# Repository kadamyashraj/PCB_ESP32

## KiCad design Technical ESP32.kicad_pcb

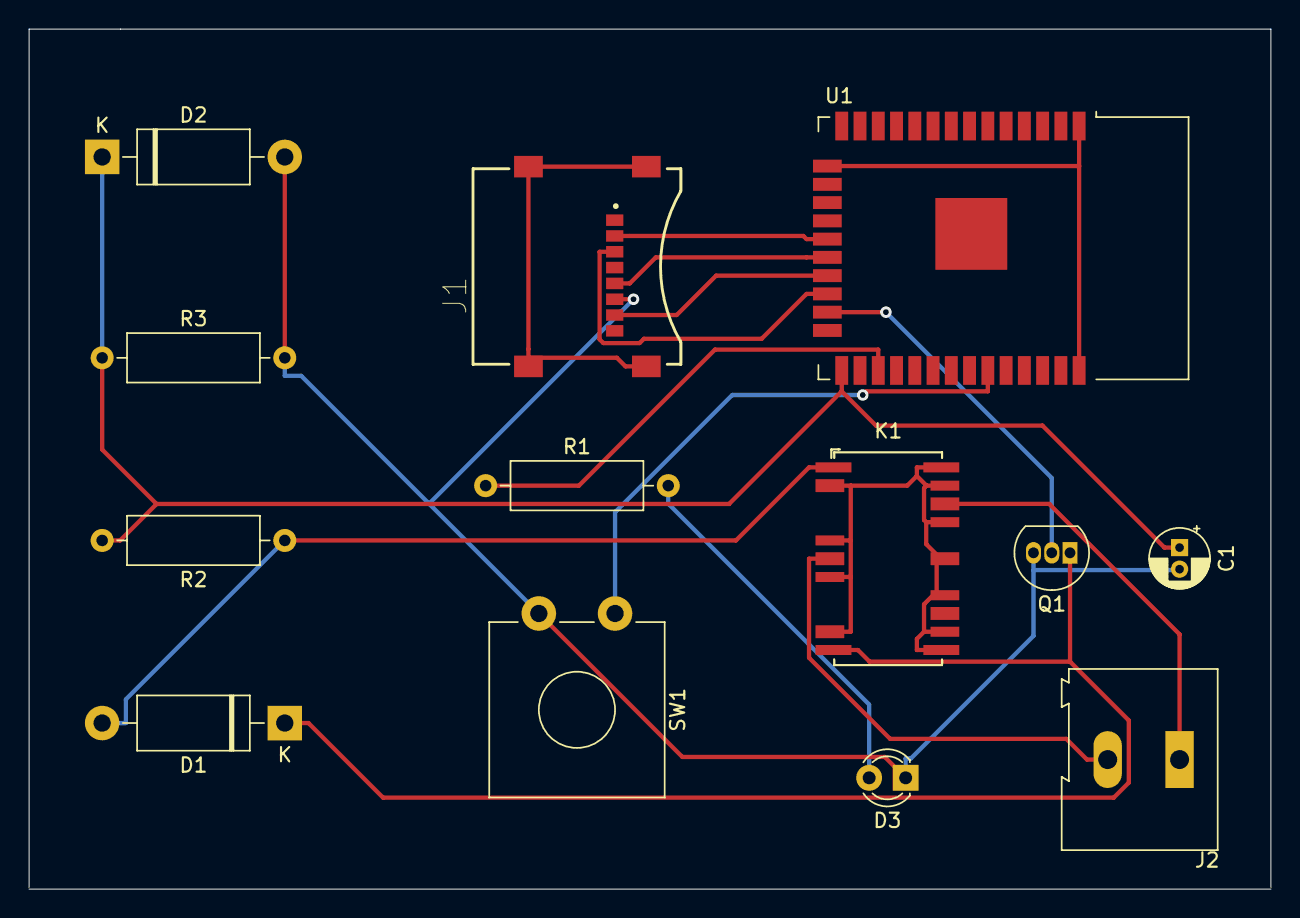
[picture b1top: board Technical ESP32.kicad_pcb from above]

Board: 2 copper layers, 86.4 x 59.8 mm, 13 parts (0 on the bottom side), 17 nets.

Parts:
C1: 1nF; CP_Radial_D4.0mm_P1.50mm
D1: DIODE; D_DO-15_P12.70mm_Horizontal
D2: 1N4723A; D_DO-15_P12.70mm_Horizontal
D3: LED; LED_D3.0mm
J1: MEM2067-02-180-00-A_REVB; GCT_MEM2067-02-180-00-A_REVB
J2: Screw_Terminal_01x02; TerminalBlock_Altech_AK300-2_P5.00mm
K1: HF3-56; Relay_SPDT_AXICOM_HF3Series_50ohms_Pitch1.27mm
Q1: BC548; TO-92_Inline
R1: 100r; R_Axial_DIN0309_L9.0mm_D3.2mm_P12.70mm_Horizontal
R2: 10k; R_Axial_DIN0309_L9.0mm_D3.2mm_P12.70mm_Horizontal
R3: 3.9k; R_Axial_DIN0309_L9.0mm_D3.2mm_P12.70mm_Horizontal
SW1: SW_Push_Open; SW_CW_GPTS203211B
U1: ESP32-WROOM-32

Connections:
+12V: D1.2, K1.1, R2.1
/InternallyPulledUp: SW1.1, U1.33
GND: C1.2, D2.2, D3.1, J1.6, Q1.3, R3.2, SW1.2
unnamed: C1.1, D2.1, R2.2, R3.1, U1.25
unnamed: D1.1, K1.11, Q1.1
unnamed: D3.2, R1.2
unnamed: J1.2, U1.19
unnamed: J1.3, U1.22
unnamed: J1.5, U1.20
unnamed: J1.7, U1.21
unnamed: J1.9, J1.10, J1.11, J1.12
unnamed: J2.1, K1.20
unnamed: J2.2, K1.6
unnamed: K1.2, K1.5, K1.7, K1.10, K1.12, K1.13, K1.15, K1.17, K1.19, K1.21, K1.22
unnamed: Q1.2, U1.23
unnamed: R1.1, U1.27
unnamed: U1.1, U1.15, U1.38
